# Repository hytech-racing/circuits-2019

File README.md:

# 2019 Circuits

## Getting Started with this git repository
1. Download and install [Github Desktop](https://desktop.github.com/) (basic) or [git](https://git-scm.com/book/en/v2/Getting-Started-Installing-Git) (advanced)
    * If you are using Github Desktop for the first time, be sure to read the [User Guide](https://help.github.com/desktop/guides/)
    * If you are using git for the first time, you should start off by reading a tutorial. There are many available online:
        * [Atlassian Git Tutorial](https://www.atlassian.com/git/tutorials/)
        * [Pro Git book](https://git-scm.com/book/en/v2)
    * You may want to keep a copy of [Github's Git Cheat Sheet](https://services.github.com/kit/downloads/github-git-cheat-sheet.pdf) as a reference
2. Create a Github account if you don't already have one
3. Talk to your subteam lead to be added to your respective team on the Github organization
4. Clone this repository to your computer
    * SSH: `git@github.com:hytech-racing/circuits-2019.git`
    * HTTPS: `https://github.com/hytech-racing/circuits-2019.git`

## Getting Started with EAGLE
1. Download and install [EAGLE](https://www.autodesk.com/products/eagle/overview)
2. Get the free [Educational License](https://www.autodesk.com/education/free-software/eagle) (a .edu email address is required)

## View on CADLAB
View design diffs on [CADLAB.io](https://cadlab.io/project/1277).

## Circuit Board Versioning Scheme
* New boards must start their numbering at revision 1.
* Revision numbers must be incremented by 1 when a physical board is manufactured.
* Revision numbers should not be incremented at any other time.
* After a board is manufactured, the files corresponding to the manufactured version should not be modified.
* Circuit boards based off of a previous year's design should increment based off of the previous board's revision number.

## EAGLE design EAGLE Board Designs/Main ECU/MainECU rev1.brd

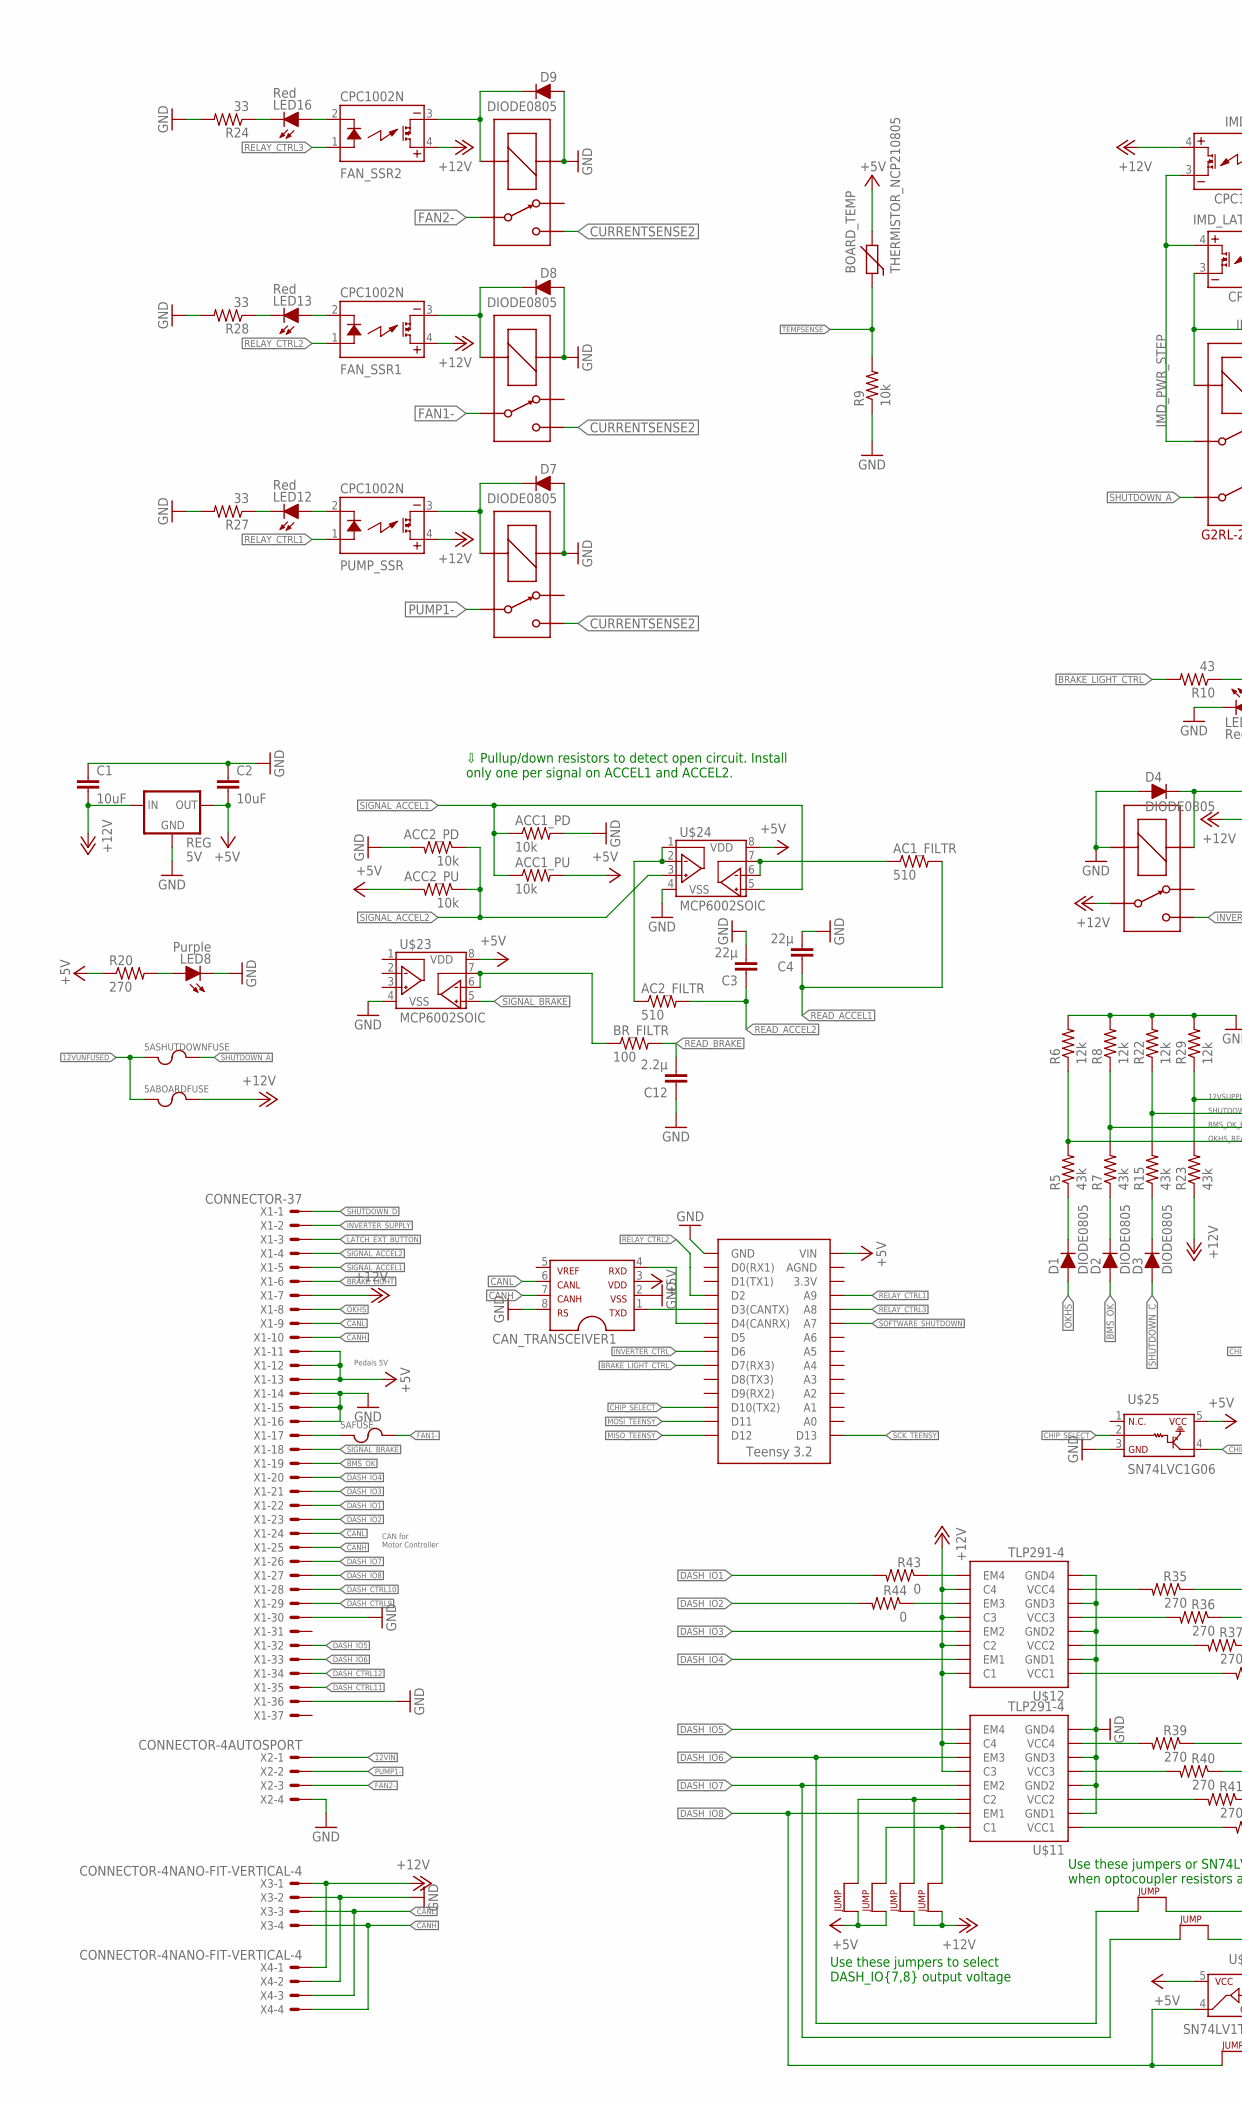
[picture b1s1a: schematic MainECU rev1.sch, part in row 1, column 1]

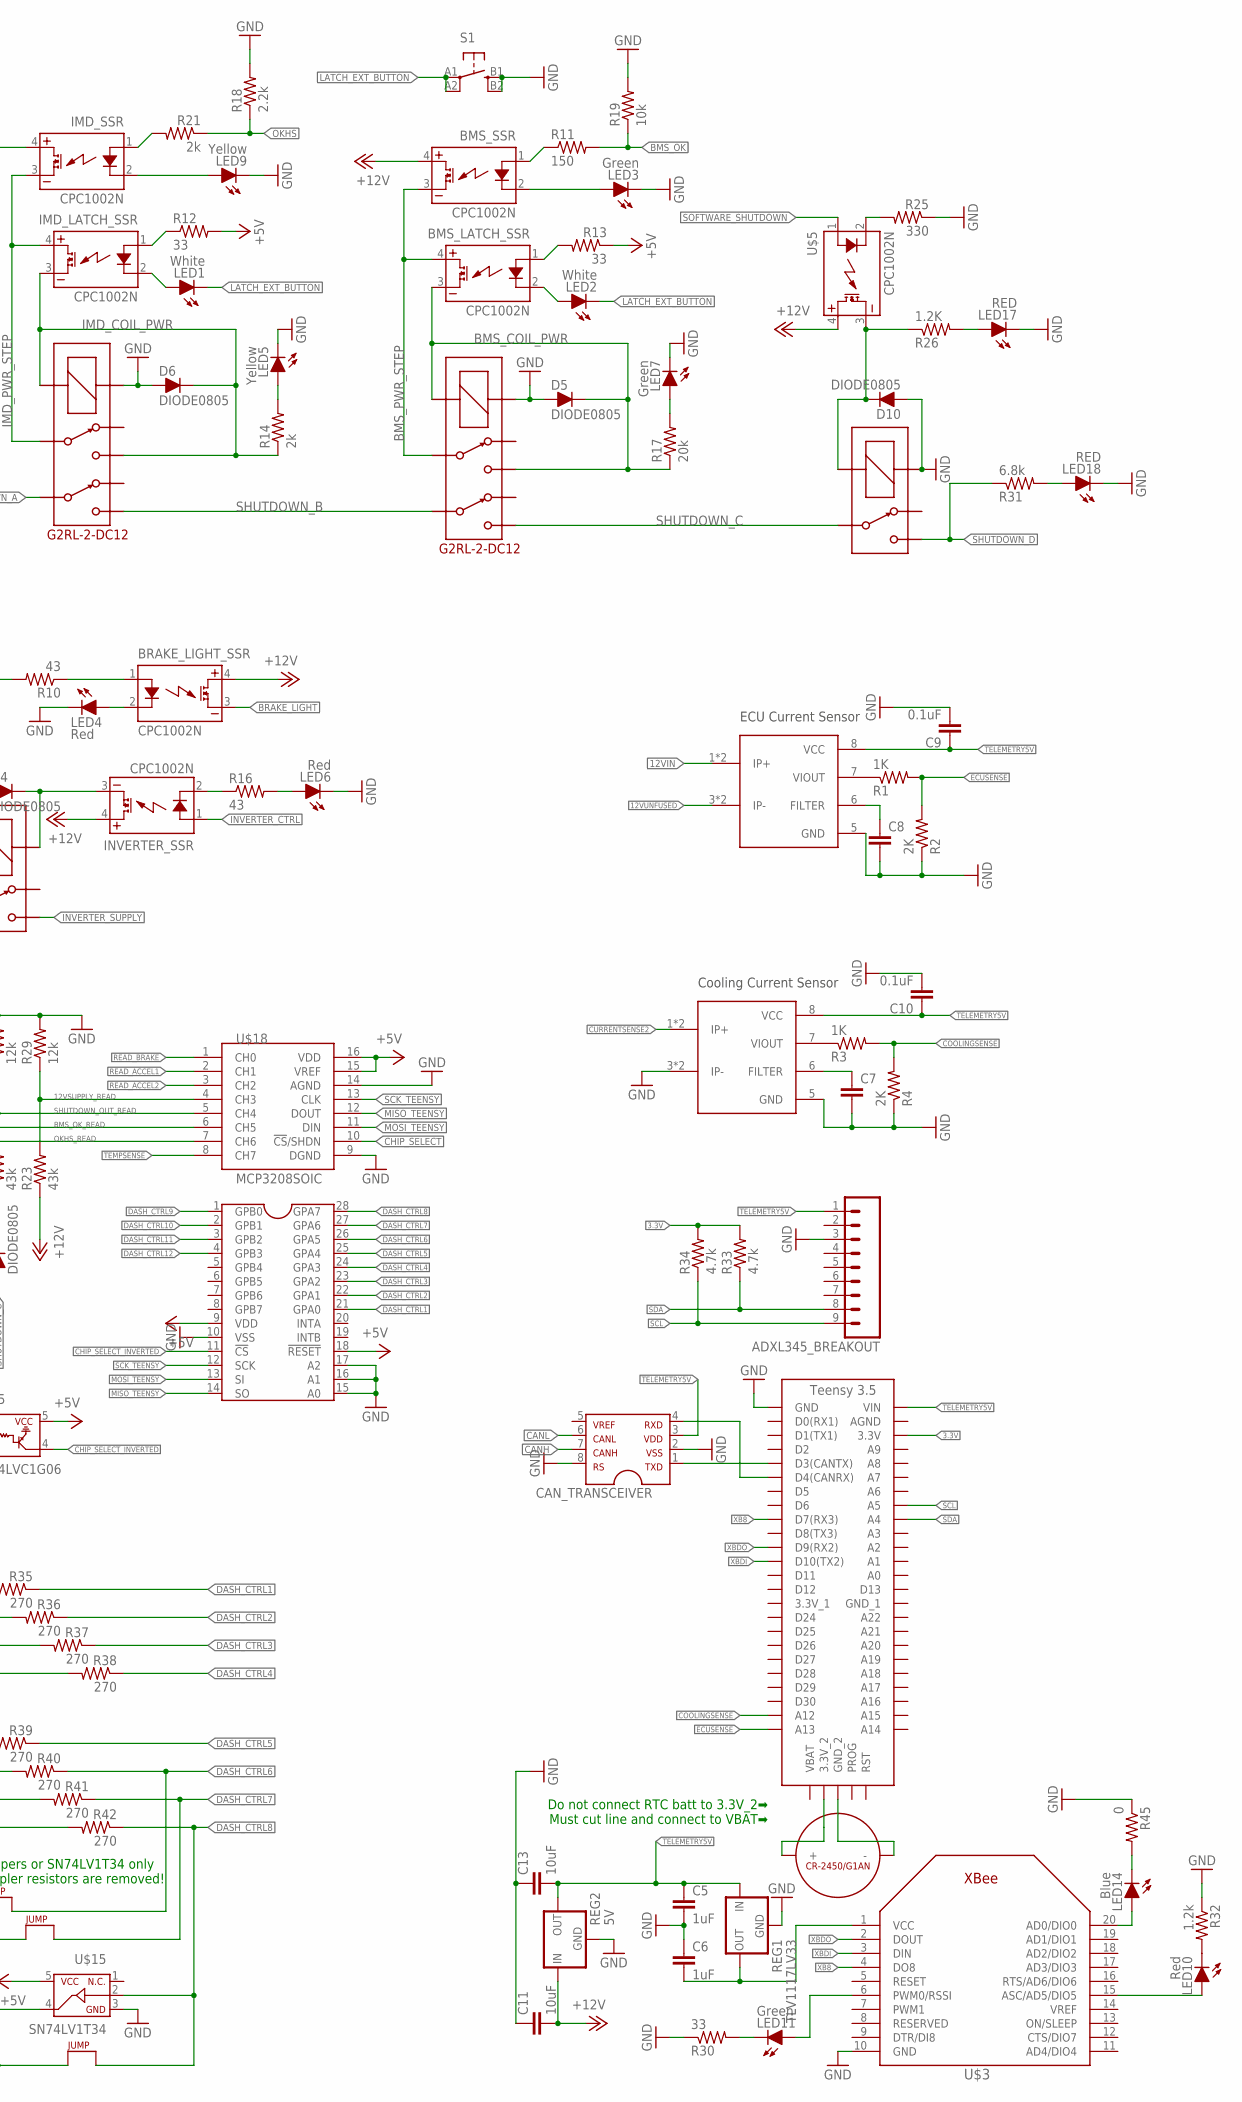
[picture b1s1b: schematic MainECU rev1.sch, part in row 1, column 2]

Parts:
5ABOARDFUSE, 5AFUSE, 5ASHUTDOWNFUSE: FUSE_MINIBLADE; MINI-BLADE_FUSE_HOLDER
AC1_FILTR, AC2_FILTR: 510; 0805
ACC1_PD, ACC1_PU, ACC2_PD, ACC2_PU: 10k; 0805
ADXL345_BREAKOUT: M09; 1X09
BMS_LATCH_SSR: CPC1002N; SOP04
BMS_SSR: CPC1002N; SOP04
BOARD_TEMP: THERMISTOR_NCP210805; 0805
BRAKE_LIGHT_SSR: CPC1002N; SOP04
BR_FILTR: 100; 0805
C1, C2, C11, C13: 10uF; 0805
C3, C4: 22µ; 0805
C5, C6: 1uF; 0805
C7, C8: CAP0805; 0805
C9, C10: 0.1uF; 0805
C12: 2.2µ; 0805
CAN_TRANSCEIVER, CAN_TRANSCEIVER1: MCP2551; SOIC-08
D1, D2, D3, D4, D5, D6, D7, D8, D9, D10: DIODE0805; 0805_D
FAN_SSR1, FAN_SSR2: CPC1002N; SOP04
IMD_LATCH_SSR: CPC1002N; SOP04
IMD_SHUTDOWN, IMD_SHUTDOWN1: G2RL-2-DC12; G2RL-2
IMD_SSR: CPC1002N; SOP04
INVERTER_SSR: CPC1002N; SOP04
LED1, LED2: White; LED-805
LED3, LED7, LED11: Green; LED-805
LED4, LED6, LED10, LED12, LED13, LED16: Red; LED-805
LED5, LED9: Yellow; LED-805
LED8: Purple; LED-805
LED14: Blue; LED-805
LED17, LED18: RED; LED-805
PUMP_SSR: CPC1002N; SOP04
R1, R3: 1K; 0805
R2, R4: 2K; 0805
R5, R7, R15, R23: 43k; 0805
R6, R8, R22, R29: 12k; 0805
R9, R19: 10k; 0805
R10, R16: 43; 0805
R11: 150; 0805
R12, R13, R24, R27, R28, R30: 33; 0805
R14, R21: 2k; 0805
R17: 20k; 0805
R18: 2.2k; 0805
R20, R35, R36, R37, R38, R39, R40, R41, R42: 270; 0805
R25: 330; 0805
R26: 1.2K; 0805
R31: 6.8k; 0805
R32: 1.2k; 0805
R33, R34: 4.7k; 0805
R43, R44, R45: 0; 0805
REG, REG2: 5V; OKI-78SR
REG1: TLV1117LV33; SOT223
S1: BTN_10-XXSMD; TACTILE_SWITCH_SMD_6.2MM_TALL
SOFTWARE_SHUTOFF: G5LE; ZF112
U$1: TEENSY_3.2_SIMPLE
U$2: TEENSY_3.5_EXT
U$3: XBEE
U$4, U$6, U$7, U$8: G5LE; ZF112
U$5: CPC1002N; SOP04
U$9, U$10: ACS715_CURRENT_SENSOR; SOP8
U$11, U$12: TLP291-4; SOIC-16
U$13, U$14, U$16, U$19, U$20, U$21, U$22: JUMPER; 0805
U$15: SN74LV1T34; SOT-23-5
U$17: MCP23S17SSOP28; SSOP28
U$18: MCP3208SOIC; SOIC-16
U$23, U$24: MCP6002SOIC; SOIC-08
U$25: SN74LVC1G06; SOT-23-5
U$26: CR-2450/G1AN
X1: CONNECTOR-37; AUTOSPORT_14-35
X2: CONNECTOR-4AUTOSPORT; AUTOSPORT_12-04
X3, X4: CONNECTOR-4NANO-FIT-VERTICAL-4; NANO-FIT_VERTICAL-4

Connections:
3.3V: R33.2, R34.2, U$2.3.3V
12VIN: U$9.1 (IP+), U$9.2 (IP+), X2.P$1
12VSUPPLY_READ: R23.2, R29.1, U$18.4 (CH3)
12VUNFUSED: 5ABOARDFUSE.L1 (1), 5ABOARDFUSE.L2 (1), 5ASHUTDOWNFUSE.L1 (1), 5ASHUTDOWNFUSE.L2 (1), U$9.3 (IP-), U$9.4 (IP-)
+5V: ACC1_PU.2, ACC2_PU.2, BOARD_TEMP.1, C2.2, CAN_TRANSCEIVER1.3, R12.2, R13.1, R20.1, REG.3 (OUT), U$1.VIN, U$15.5, U$17.9 (VDD), U$17.18 (!RESET), U$18.15 (VREF), U$18.16 (VDD), U$20.1, U$22.1, U$23.8 (VDD), U$24.8 (VDD), U$25.5, X1.P$11, X1.P$12, X1.P$13
+12V: 5ABOARDFUSE.R1 (2), 5ABOARDFUSE.R2 (2), BMS_SSR.4 (DC+), BRAKE_LIGHT_SSR.4 (DC+), C1.2, C11.2, FAN_SSR1.4 (DC+), FAN_SSR2.4 (DC+), IMD_SSR.4 (DC+), INVERTER_SSR.4 (DC+), PUMP_SSR.4 (DC+), R23.1, REG.1 (IN), REG2.1 (IN), U$5.4 (DC+), U$8.P, U$11.10 (C4), U$11.12 (C3), U$12.10 (C4), U$12.12 (C3), U$12.14 (C2), U$12.16 (C1), U$16.1, U$21.1, X1.P$7, X3.P$1, X4.P$1
BMS_COIL_PWR: BMS_LATCH_SSR.3 (DC-), D5.C, IMD_SHUTDOWN1.4, IMD_SHUTDOWN1.COIL-, R17.1
BMS_OK: D2.A, R11.2, R19.1, X1.P$19
BMS_OK_READ: R7.2, R8.1, U$18.6 (CH5)
BMS_PWR_STEP: BMS_LATCH_SSR.4 (DC+), BMS_SSR.3 (DC-), IMD_SHUTDOWN1.3
BRAKE_LIGHT: BRAKE_LIGHT_SSR.3 (DC-), X1.P$6
BRAKE_LIGHT_CTRL: R10.2, U$1.D7(RX3)
CANH: CAN_TRANSCEIVER.7, CAN_TRANSCEIVER1.7, X1.P$10, X1.P$25, X3.P$4, X4.P$4
CANL: CAN_TRANSCEIVER.6, CAN_TRANSCEIVER1.6, X1.P$9, X1.P$24, X3.P$3, X4.P$3
CHIP_SELECT: U$1.D10(TX2), U$18.10 (!CS!/SHDN), U$25.2
CHIP_SELECT_INVERTED: U$17.11 (!CS), U$25.4
COOLINGSENSE: R3.2, R4.2, U$2.A12
CURRENTSENSE2: U$4.S, U$6.S, U$7.S, U$10.1 (IP+), U$10.2 (IP+)
DASH_CTRL1: R35.1, U$17.21 (GPA0)
DASH_CTRL2: R36.1, U$17.22 (GPA1)
DASH_CTRL3: R37.1, U$17.23 (GPA2)
DASH_CTRL4: R38.1, U$17.24 (GPA3)
DASH_CTRL5: R39.1, U$17.25 (GPA4)
DASH_CTRL6: R40.1, U$13.2, U$17.26 (GPA5)
DASH_CTRL7: R41.1, U$14.2, U$17.27 (GPA6)
DASH_CTRL8: R42.1, U$15.2, U$17.28 (GPA7), U$19.2
DASH_CTRL9: U$17.1 (GPB0), X1.P$29
DASH_CTRL10: U$17.2 (GPB1), X1.P$28
DASH_CTRL11: U$17.3 (GPB2), X1.P$35
DASH_CTRL12: U$17.4 (GPB3), X1.P$34
DASH_IO1: R43.2, X1.P$22
DASH_IO2: R44.2, X1.P$23
DASH_IO3: U$12.13 (EM2), X1.P$21
DASH_IO4: U$12.15 (EM1), X1.P$20
DASH_IO5: U$11.9 (EM4), X1.P$32
DASH_IO6: U$11.11 (EM3), U$13.1, X1.P$33
DASH_IO7: U$11.13 (EM2), U$14.1, X1.P$26
DASH_IO8: U$11.15 (EM1), U$15.4, U$19.1, X1.P$27
ECUSENSE: R1.2, R2.2, U$2.A13
FAN1-: 5AFUSE.R1 (2), 5AFUSE.R2 (2), U$7.P
FAN2-: U$4.P, X2.P$3
GND: ACC1_PD.2, ACC2_PD.2, ADXL345_BREAKOUT.3, C1.1, C2.1, C3.2, C4.2, C5.2, C6.1, C7.2, C8.2, C9.2, C10.2, C11.1, C12.1, C13.1, CAN_TRANSCEIVER.2, CAN_TRANSCEIVER.8, CAN_TRANSCEIVER1.2, CAN_TRANSCEIVER1.8, D4.A, D5.A, D6.A, D7.A, D8.A, D9.A, D10.A, IMD_SHUTDOWN.COIL+, IMD_SHUTDOWN1.COIL+, LED3.C, LED4.C, LED5.C, LED6.C, LED7.C, LED8.C, LED9.C, LED17.C, LED18.C, R2.1, R4.1, R6.2, R8.2, R9.1, R18.2, R19.2, R22.2, R24.2, R25.1, R27.2, R28.2, R29.2, R30.1, R32.1, R45.1, REG.2 (GND), REG1.1 (GND), REG2.2 (GND), S1.B1 (S), S1.B2 (S1), SOFTWARE_SHUTOFF.1 (COIL+), U$1.GND, U$2.GND, U$3.10 (GND), U$4.1 (COIL+), U$6.1 (COIL+), U$7.1 (COIL+), U$8.2 (COIL-), U$9.5 (GND), U$10.3 (IP-), U$10.4 (IP-), U$10.5 (GND), U$11.2 (GND1), U$11.4 (GND2), U$11.6 (GND3), U$11.8 (GND4), U$12.2 (GND1), U$12.4 (GND2), U$12.6 (GND3), U$12.8 (GND4), U$15.3, U$17.10 (VSS), U$17.15 (A0), U$17.16 (A1), U$17.17 (A2), U$18.9 (DGND), U$18.14 (AGND), U$23.4 (VSS), U$24.4 (VSS), U$25.3, X1.P$14, X1.P$15, X1.P$16, X1.P$30, X1.P$36, X2.P$4, X3.P$2, X4.P$2
IMD_COIL_PWR: D6.C, IMD_LATCH_SSR.3 (DC-), IMD_SHUTDOWN.4, IMD_SHUTDOWN.COIL-, R14.1
IMD_PWR_STEP: IMD_LATCH_SSR.4 (DC+), IMD_SHUTDOWN.3, IMD_SSR.3 (DC-)
INVERTER_CTRL: INVERTER_SSR.1 (CONTROL+), U$1.D6
INVERTER_SUPPLY: U$8.S, X1.P$2
LATCH_EXT_BUTTON: LED1.C, LED2.C, S1.A1, S1.A2 (P1), X1.P$3
MISO_TEENSY: U$1.D12, U$17.14 (SO), U$18.12 (DOUT)
MOSI_TEENSY: U$1.D11, U$17.13 (SI), U$18.11 (DIN)
unnamed: 5AFUSE.L1 (1), 5AFUSE.L2 (1), X1.P$17
unnamed: IMD_LATCH_SSR.2 (CONTROL-), LED1.A
unnamed: R1.1, U$9.7 (VIOUT)
unnamed: D7.C, PUMP_SSR.3 (DC-), U$6.2 (COIL-)
unnamed: IMD_LATCH_SSR.1 (CONTROL+), R12.1
unnamed: R3.1, U$10.7 (VIOUT)
unnamed: BRAKE_LIGHT_SSR.2 (CONTROL-), LED4.A
unnamed: C8.1, U$9.6 (FILTER)
unnamed: BMS_SSR.2 (CONTROL-), LED3.A
unnamed: D1.C, R5.1
unnamed: D2.C, R7.1
unnamed: BMS_LATCH_SSR.1 (CONTROL+), R13.2
unnamed: CAN_TRANSCEIVER.4, U$2.D4(CANRX)
unnamed: CAN_TRANSCEIVER.1, U$2.D3(CANTX)
unnamed: CAN_TRANSCEIVER1.4, U$1.D4(CANRX)
unnamed: BMS_LATCH_SSR.2 (CONTROL-), LED2.A
unnamed: BRAKE_LIGHT_SSR.1 (CONTROL+), R10.1
unnamed: BMS_SSR.1 (CONTROL+), R11.1
unnamed: LED5.A, R14.2
unnamed: D8.C, FAN_SSR1.3 (DC-), U$7.2 (COIL-)
unnamed: D9.C, FAN_SSR2.3 (DC-), U$4.2 (COIL-)
unnamed: CAN_TRANSCEIVER1.1, U$1.D3(CANTX)
unnamed: AC2_FILTR.1, U$24.1 (VOUTA), U$24.2 (VINA-)
unnamed: AC1_FILTR.1, U$24.6 (VINB-), U$24.7 (VOUTB)
unnamed: BR_FILTR.1, U$23.6 (VINB-), U$23.7 (VOUTB)
unnamed: D4.C, INVERTER_SSR.3 (DC-), U$8.1 (COIL+)
unnamed: INVERTER_SSR.2 (CONTROL-), R16.1
unnamed: LED6.A, R16.2
unnamed: LED8.A, R20.2
unnamed: LED16.C, R24.1
unnamed: IMD_SSR.1 (CONTROL+), R21.2
unnamed: LED7.A, R17.2
unnamed: D3.C, R15.1
unnamed: IMD_SSR.2 (CONTROL-), LED9.A
unnamed: LED14.C, R45.2
unnamed: LED13.C, R28.1
unnamed: LED12.C, R27.1
unnamed: LED12.A, PUMP_SSR.2 (CONTROL-)
unnamed: FAN_SSR2.2 (CONTROL-), LED16.A
unnamed: LED18.A, R31.2
unnamed: U$2.3.3V_2, U$26.+_0 (+), U$26.+_1 (+)
unnamed: FAN_SSR1.2 (CONTROL-), LED13.A
unnamed: D10.C, R26.1, SOFTWARE_SHUTOFF.2 (COIL-), U$5.3 (DC-)
unnamed: R25.2, U$5.2 (CONTROL-)
unnamed: LED11.C, R30.2
unnamed: LED17.A, R26.2
unnamed: LED11.A, U$3.6 (PWM0/RSSI)
unnamed: C7.1, U$10.6 (FILTER)
unnamed: LED10.A, U$3.15 (ASC/AD5/DIO5)
unnamed: LED10.C, R32.2
unnamed: R35.2, U$12.7 (VCC4)
unnamed: R36.2, U$12.5 (VCC3)
unnamed: R37.2, U$12.3 (VCC2)
unnamed: R38.2, U$12.1 (VCC1)
unnamed: R39.2, U$11.7 (VCC4)
unnamed: R40.2, U$11.5 (VCC3)
unnamed: R41.2, U$11.3 (VCC2)
unnamed: R42.2, U$11.1 (VCC1)
unnamed: R43.1, U$12.9 (EM4)
unnamed: R44.1, U$12.11 (EM3)
unnamed: U$11.16 (C1), U$16.2, U$20.2
unnamed: U$11.14 (C2), U$21.2, U$22.2
unnamed: LED14.A, U$3.20 (AD0/DIO0)
unnamed: U$2.GND_2, U$26.-
OKHS: D1.A, R18.1, R21.1, X1.P$8
OKHS_READ: R5.2, R6.1, U$18.7 (CH6)
PUMP1-: U$6.P, X2.P$2
READ_ACCEL1: AC1_FILTR.2, C4.1, U$18.2 (CH1)
READ_ACCEL2: AC2_FILTR.2, C3.1, U$18.3 (CH2)
READ_BRAKE: BR_FILTR.2, C12.2, U$18.1 (CH0)
RELAY_CTRL1: PUMP_SSR.1 (CONTROL+), U$1.A9
RELAY_CTRL2: FAN_SSR1.1 (CONTROL+), U$1.D2
RELAY_CTRL3: FAN_SSR2.1 (CONTROL+), U$1.A8
SCK_TEENSY: U$1.D13, U$17.12 (SCK), U$18.13 (CLK)
SCL: ADXL345_BREAKOUT.9, R34.1, U$2.A5
SDA: ADXL345_BREAKOUT.8, R33.1, U$2.A4
SHUTDOWN_A: 5ASHUTDOWNFUSE.R1 (2), 5ASHUTDOWNFUSE.R2 (2), IMD_SHUTDOWN.6
SHUTDOWN_B: IMD_SHUTDOWN.5, IMD_SHUTDOWN1.6
SHUTDOWN_C: D3.A, IMD_SHUTDOWN1.5, SOFTWARE_SHUTOFF.P
SHUTDOWN_D: R31.1, SOFTWARE_SHUTOFF.S, X1.P$1
SHUTDOWN_OUT_READ: R15.2, R22.1, U$18.5 (CH4)
SIGNAL_ACCEL1: ACC1_PD.1, ACC1_PU.1, U$24.5 (VINB+), X1.P$5
SIGNAL_ACCEL2: ACC2_PD.1, ACC2_PU.1, U$24.3 (VINA+), X1.P$4
SIGNAL_BRAKE: U$23.5 (VINB+), X1.P$18
SOFTWARE_SHUTDOWN: U$1.A7, U$5.1 (CONTROL+)
TELEMETRY5V: ADXL345_BREAKOUT.1, C5.1, C9.1, C10.1, C13.2, CAN_TRANSCEIVER.3, REG1.3 (IN), REG2.3 (OUT), U$2.VIN, U$9.8 (VCC), U$10.8 (VCC)
TEMPSENSE: BOARD_TEMP.2, R9.2, U$18.8 (CH7)
VCC: C6.2, REG1.2 (OUT), REG1.4 (OUT), U$3.1 (VCC)
XB8: U$2.D7(RX3), U$3.4 (DO8)
XBDI: U$2.D10(TX2), U$3.3 (DIN)
XBDO: U$2.D9(RX2), U$3.2 (DOUT)

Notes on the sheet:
ECU Current Sensor
Cooling Current Sensor
⇩ Pullup/down resistors to detect open circuit. Install only one per signal on ACCEL1 and ACCEL2.
Use these jumpers or SN74LV1T34 only when optocoupler resistors are removed!
Use these jumpers to select DASH_IO{7,8} output voltage
Pedals 5V
CAN for Motor Controller
Do not connect RTC batt to 3.3V_2➡ Must cut line and connect to VBAT➡

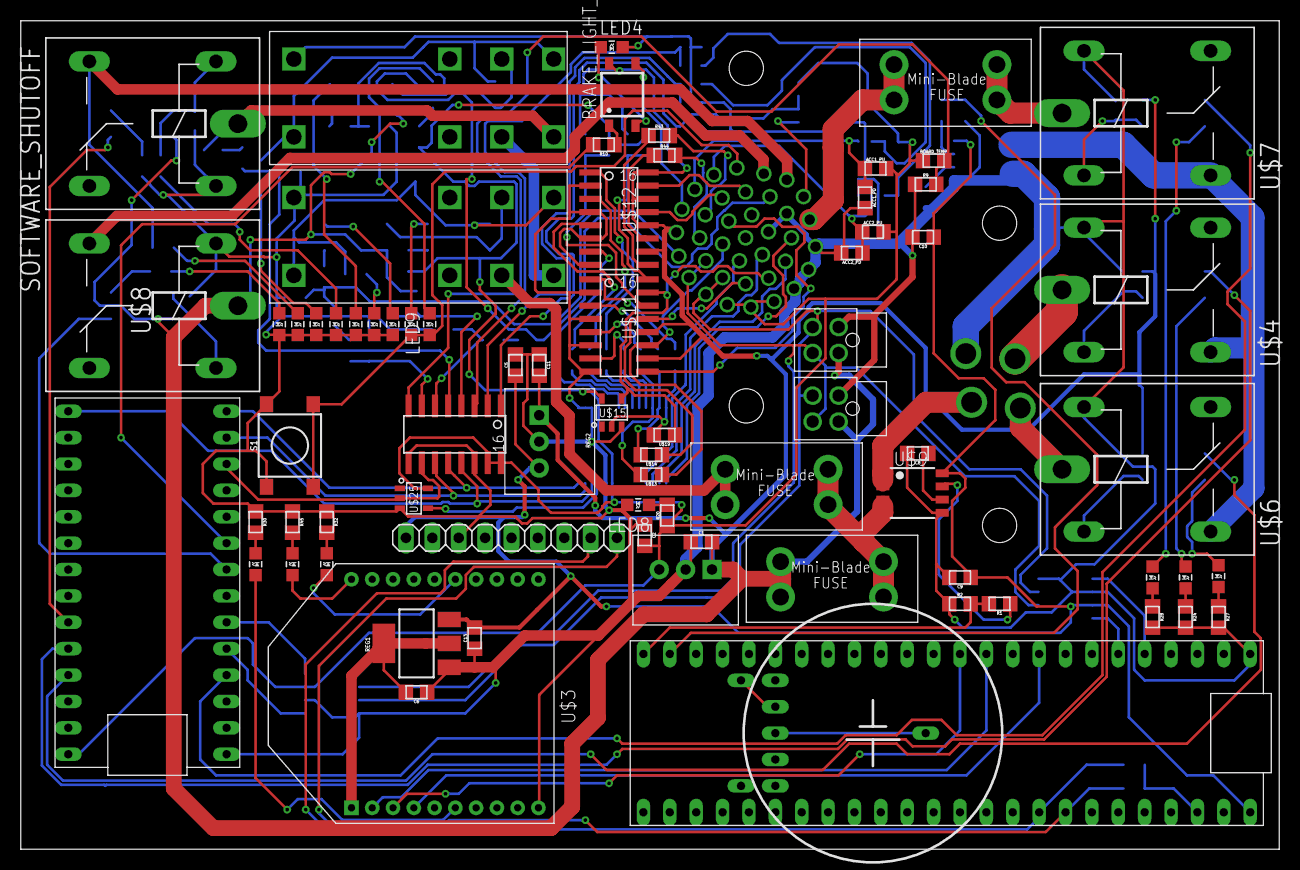
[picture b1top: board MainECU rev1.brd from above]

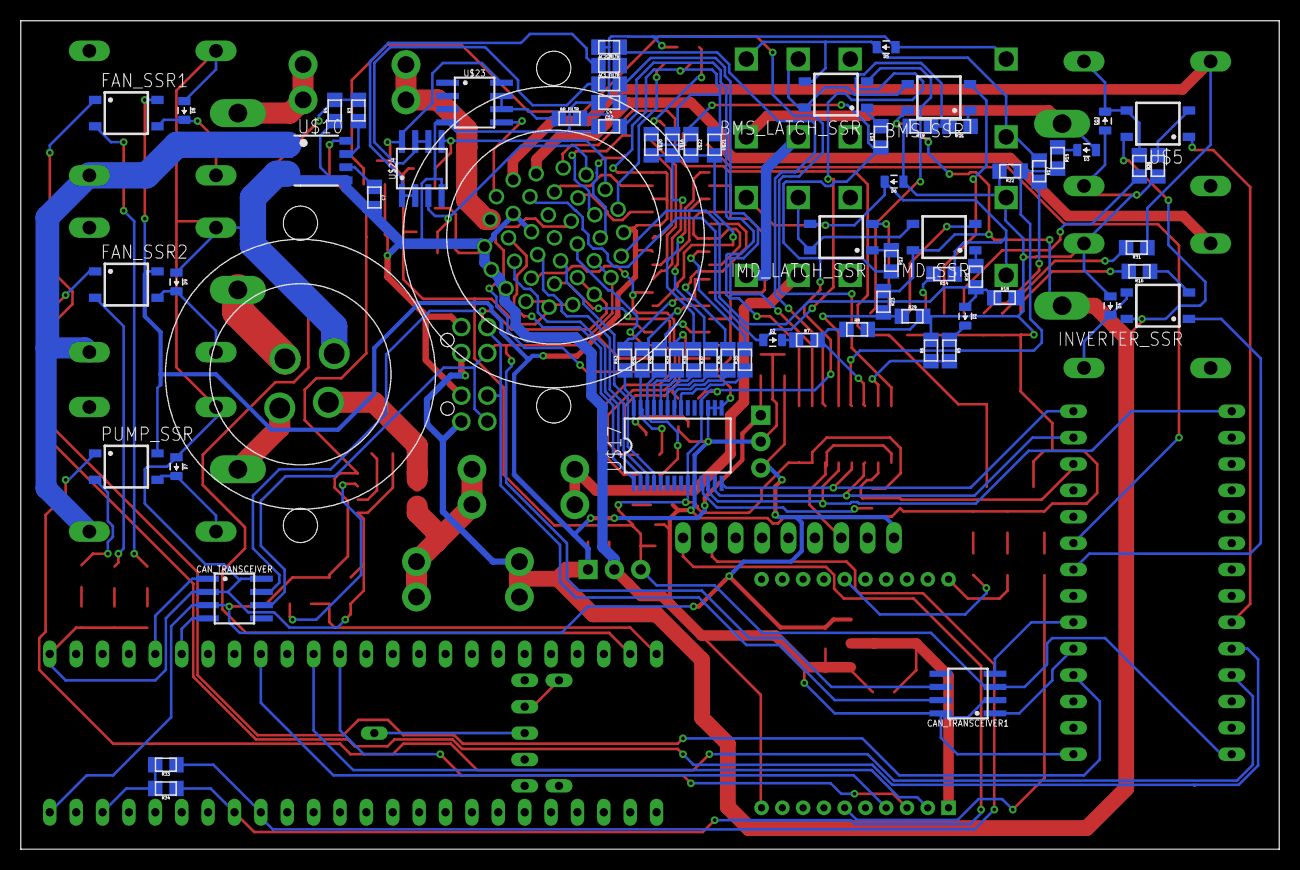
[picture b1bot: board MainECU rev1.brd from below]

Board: 2 copper layers, 121.2 x 79.8 mm, 145 parts (70 on the bottom side), 140 nets.
